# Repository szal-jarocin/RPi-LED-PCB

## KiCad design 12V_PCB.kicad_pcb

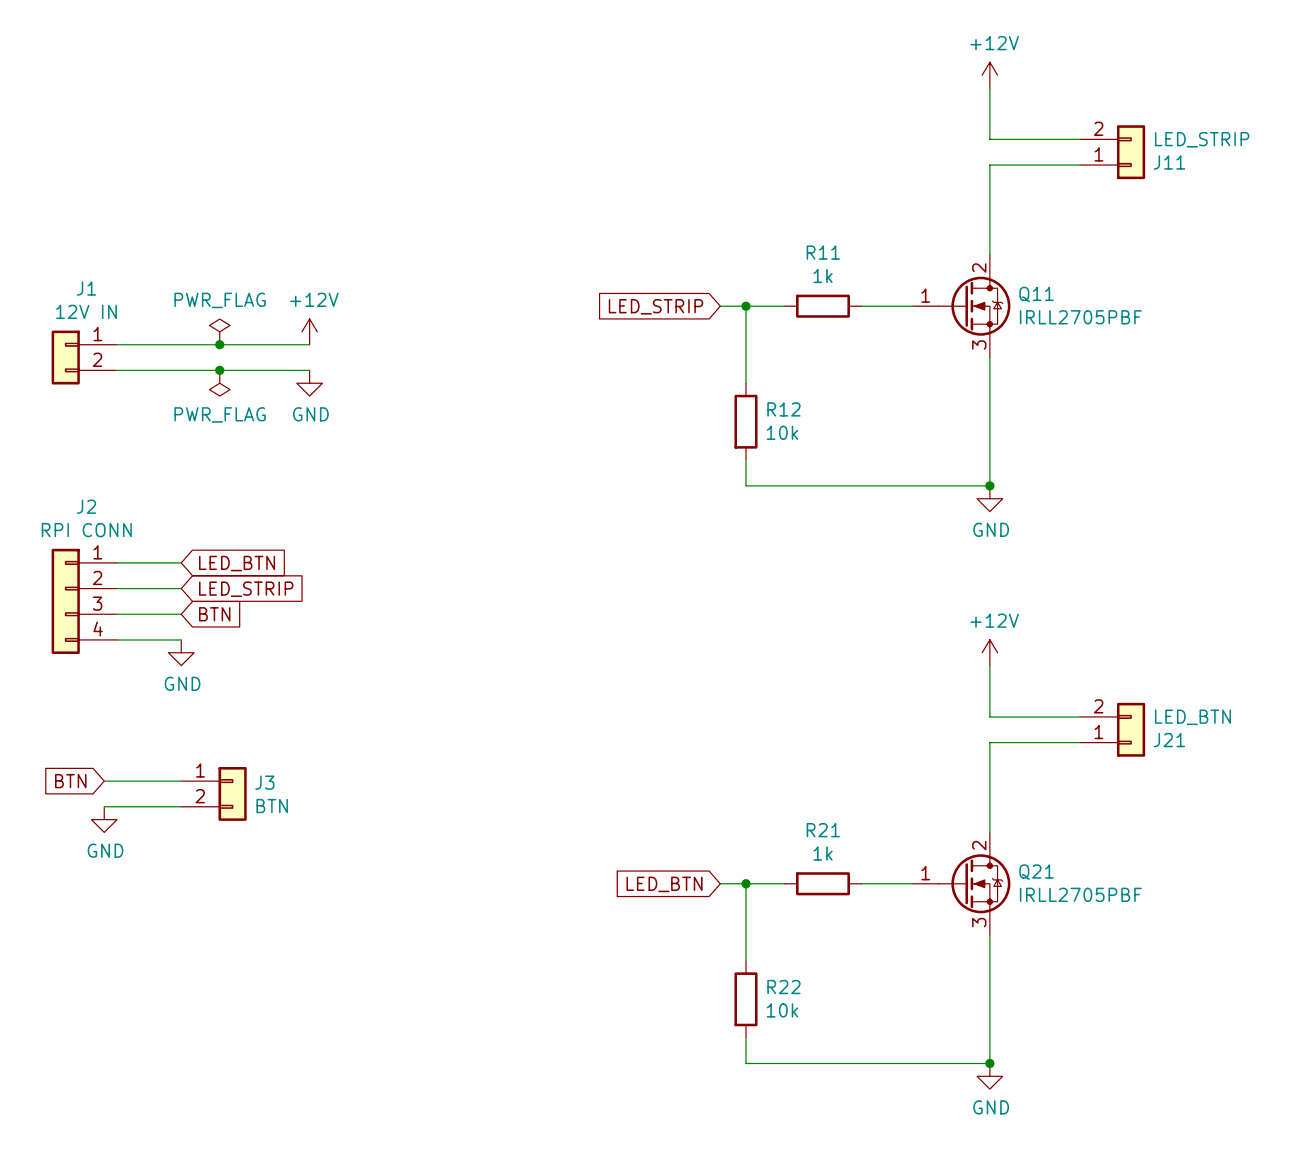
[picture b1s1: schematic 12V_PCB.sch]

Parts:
J1: 12V IN; BarrelJack_Horizontal
J2: RPI CONN; PinSocket_1x04_P2.54mm_Vertical
J3: BTN; Molex_KK-254_AE-6410-02A_1x02_P2.54mm_Vertical
J11: LED_STRIP; Molex_KK-254_AE-6410-02A_1x02_P2.54mm_Vertical
J21: LED_BTN; Molex_KK-254_AE-6410-02A_1x02_P2.54mm_Vertical
Q11, Q21: IRLL2705PBF; SOT-223-3_TabPin2
R11: 1k; R_0603_1608Metric_Pad1.05x0.95mm_HandSolder
R12: 10k; R_0603_1608Metric_Pad1.05x0.95mm_HandSolder
R21: 1k; R_0603_1608Metric_Pad0.98x0.95mm_HandSolder
R22: 10k; R_0603_1608Metric_Pad0.98x0.95mm_HandSolder

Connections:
+12V: J1.1, J11.2, J21.2
BTN: J2.3, J3.1
GND: J1.2, J2.4, J3.2, Q11.3 (S), Q21.3 (S), R12.2, R22.2
LED_BTN: J2.1, R21.2, R22.1
LED_STRIP: J2.2, R11.2, R12.1
unnamed: J11.1, Q11.2 (D)
unnamed: J21.1, Q21.2 (D)
unnamed: Q11.1 (G), R11.1
unnamed: Q21.1 (G), R21.1

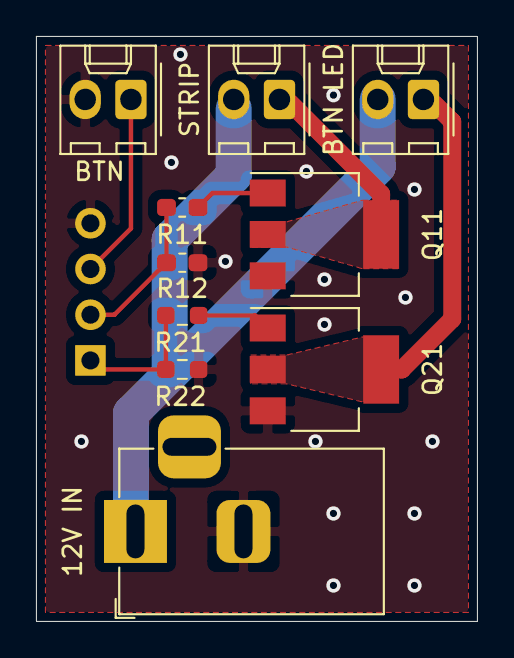
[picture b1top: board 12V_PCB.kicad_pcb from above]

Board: 2 copper layers, 24.5 x 32.5 mm, 11 parts (1 on the bottom side), 9 nets.

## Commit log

2022-05-05 added LED_BTN section
2022-06-05 Final version with panelization
